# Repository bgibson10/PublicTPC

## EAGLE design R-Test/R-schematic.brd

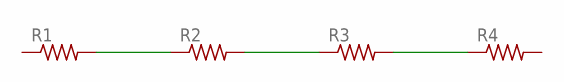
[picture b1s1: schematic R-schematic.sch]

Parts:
R1, R2, R3, R4: R-US_M1206; M1206

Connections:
PAD$A1: R1.2, R2.1
PAD$B1: R3.2, R4.1
PAD$C1: R2.2, R3.1

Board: 2 copper layers, 4 parts (0 on the bottom side), 3 nets, no tracks yet.

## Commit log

2017-10-05 Remove some fat
    Removal of old comments
2017-10-05 Cover Layer Creation
    file to create the cover layer that will be set over the resistors
2017-10-08 (Added) To Do List
    to do list for this project and possible upcoming
2017-10-08 Removed Ppt
2017-10-08 dds
    dds
2017-10-21 Workable edition of CoverLayer created
    Will start to test
2017-10-23 Now runs and gives a usable output
    To be tested next
2017-10-23 Add end to signals
2017-10-23 Attempt at fixing the origin problem
    would not line up, but flip over axis. This should be a fix.
2017-10-23 Possible fix to origin problem
2017-10-23 Attempt 2, removal of Plain
2017-11-01 fixed the extra side
2017-11-02 forgot stuff
    Forgot to have the last x change
2017-11-02 Delete CoverLayerOutput.brd
    put in wrong place
2017-11-02 Placed into right folder
2017-11-02 Get the negative right....
2017-11-02 Corrected corners?
    attempt to fix the corners, the origin still needs to be fixed, but the shape is perfect now
2017-11-02 attempt at fixing the curved inners
2017-11-02 Attempt 2 at curves
2017-11-07 origin switch
2017-11-07 origins
2017-11-07 origing
2017-11-07 stuff
2017-11-07 fixed curves?
2017-11-07 reset curves
2017-11-21 updates
    new origins, correct segment measurments, and other stuff
